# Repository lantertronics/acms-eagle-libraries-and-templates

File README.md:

Here's a set of Eagle files for the benefit of my ECE4450: Analog Circuits for Music Synthesis studnets; hopefully other folks will find them helpful as well.

# Spring 2023: Tangible Waves template

To use acms_project_starter_template, I recommend copying the schematic file and giving it a new filename and deleting the parts you don't need, but *not* copying the board file. Official tangible waves modules use surface mount parts for manufacturability and to keep the size small. Since we're using through-hole parts, we need more space, so I made it three Tangible Waves module units wide (75 millimeters). You can try making this 50 millimeters wide instead if you have a small circuit (change the width to 1.9685 inches and delete the two rightmost mounting holes and then scoot the headers over).

# Spring 2021: Eurorack/MOTM template

To use acms_project_starter_template, I recommend copying the schematic file and giving it a new filename and deleting the parts you don't need, but *not* copying the board file. The board file shows where to put mounting holes (size 0.12587425 = 3.2 mm), but otherwise isn't too useful, since once you start adding your own parts, Eagle will just plunk them down one after another in a straight line going downward. If you place your parts on the schematic first and then tell Eagle to make the PCB, the parts will appear in a nice convenient grid pattern on the side of the PCB.

# Libraries

ota_upgraded.lbr and synthdiy_upgraded.lbr are librraries I found elsewhere that didn't want to open in the newest version of Eagle; apparently the name for layer 88 got scrabled as part of the input process. I just changed the layer name to "weird" to get something that would import without error.

The devices in the aaronXXXX.lbr libraries all have the suffix _AARON; I did that so I can find my custom devices quickly.

The capacitors in the eagle library have a little capacitor symbol on the PCB footprint, and have the cap value outside. I prefer to put the cap value inside the symbol footprint, so I made aaroncap.lbr, which has some capacitor footprints with the cap symbol removed and the value placed inside the capacitor.

aaronlibrary.lbr has an oval PCB pad with a little X for the schematic symbol (IOPAD_AARON), a jack symbol on the schematic for off-board jacks where the PCB has a circular pad for the signal and a square pad for the ground (OFFBOARD2JACKALT_AARON), and symbols for the SSM2210 and SSM2220 matched transistor pairs.

I made aaronpot.lbr to handle some potentiometers where I couldn't find a built-in Eagle symbol that exactly matched it. I can't remember exactly what I made it for.

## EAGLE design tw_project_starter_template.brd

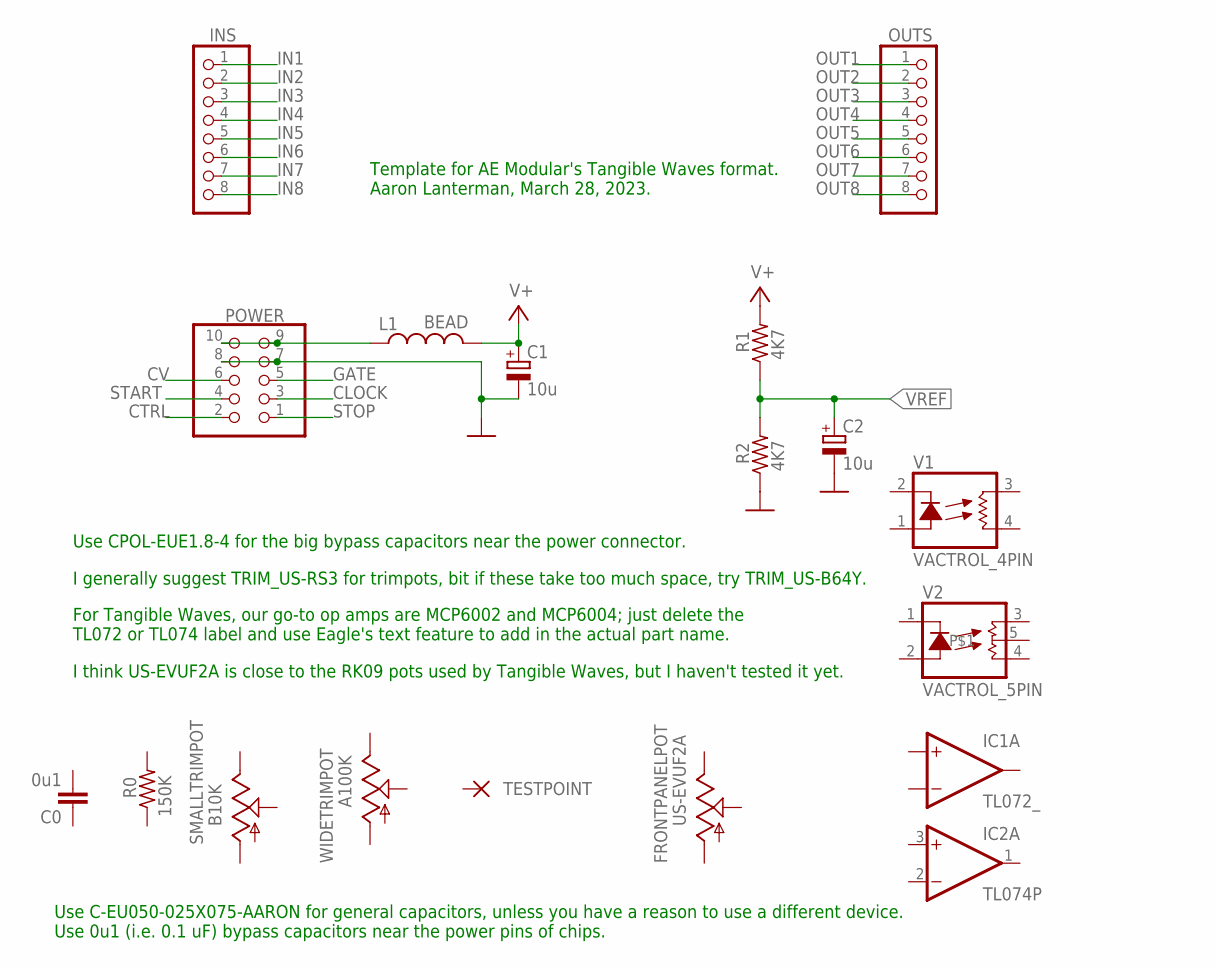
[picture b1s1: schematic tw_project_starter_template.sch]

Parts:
C0: 0u1; C050-025X075-AARON
C1, C2: 10u; E1,8-4
FRONTPANELPOT: US-EVUF2A; EVUF
IC1: TL072_; DIL08
IC2: TL074P; DIL14
INS: PINHD-1X8; 1X08
L1: BEAD; 0207/10
OUTS: PINHD-1X8; 1X08
POWER: PINHD-2X5; 2X05
R0: 150K; 0207/10
R1, R2: 4K7; 0207/10
SMALLTRIMPOT: B10K; B64Y
TESTPOINT: IOPAD_AARON; ELLIPTICALPADSINGLE
V1: VACTROL_4PIN; VACTROL_4PIN_VTL5C
V2: VACTROL_5PIN; VACTROL_5PIN_VTL5C-2
WIDETRIMPOT: A100K; S63P

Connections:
+5V: L1.1, POWER.9, POWER.10
CLOCK: POWER.3
CTRL: POWER.2
CV: POWER.6
GATE: POWER.5
GND: C1.-, C2.-, POWER.7, POWER.8, R2.1
IN1: INS.1
IN2: INS.2
IN3: INS.3
IN4: INS.4
IN5: INS.5
IN6: INS.6
IN7: INS.7
IN8: INS.8
OUT1: OUTS.1
OUT2: OUTS.2
OUT3: OUTS.3
OUT4: OUTS.4
OUT5: OUTS.5
OUT6: OUTS.6
OUT7: OUTS.7
OUT8: OUTS.8
START: POWER.4
STOP: POWER.1
V+: C1.+, IC1.8 (V+), IC2.4 (V+), L1.2, R1.2
V-: IC1.4 (V-), IC2.11 (V-)
VREF: C2.+, R1.1, R2.2

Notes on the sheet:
Template for AE Modular's Tangible Waves format. Aaron Lanterman, March 28, 2023.
Use CPOL-EUE1.8-4 for the big bypass capacitors near the power connector.
Use C-EU050-025X075-AARON for general capacitors, unless you have a reason to use a different device. Use 0u1 (i.e. 0.1 uF) bypass capacitors near the power pins of chips.
I generally suggest TRIM_US-RS3 for trimpots, bit if these take too much space, try TRIM_US-B64Y.
For Tangible Waves, our go-to op amps are MCP6002 and MCP6004; just delete the TL072 or TL074 label and use Eagle's text feature to add in the actual part name.
I think US-EVUF2A is close to the RK09 pots used by Tangible Waves, but I haven't tested it yet.

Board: 2 copper layers, 18 parts (0 on the bottom side), 5 nets, no tracks yet.

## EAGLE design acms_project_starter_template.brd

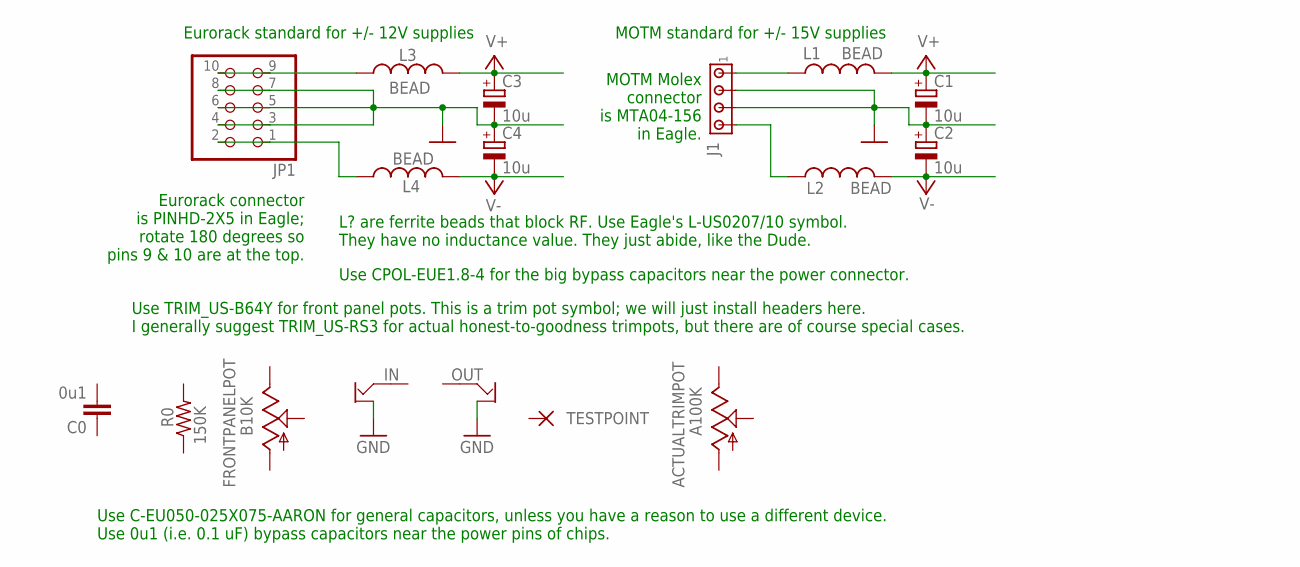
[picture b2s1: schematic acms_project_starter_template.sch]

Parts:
ACTUALTRIMPOT: A100K; RS3
C0: 0u1; C050-025X075-AARON
C1, C2, C3, C4: 10u; E1,8-4
FRONTPANELPOT: B10K; B64Y
IN: OFFBOARD2JACKALT_AARON; OFFBOARD2JACKALT
J1: MTA04-156; 1X4MTA
JP1: PINHD-2X5; 2X05
L1, L2, L3, L4: BEAD; 0207/10
OUT: OFFBOARD2JACKALT_AARON; OFFBOARD2JACKALT
R0: 150K; 0207/10
TESTPOINT: IOPAD_AARON; ELLIPTICALPADSINGLE

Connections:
GND: C1.-, C2.+, C3.-, C4.+, IN.GND, J1.2, J1.3, JP1.3, JP1.4, JP1.5, JP1.6, JP1.7, JP1.8, OUT.GND
unnamed: J1.1, L1.1
unnamed: J1.4, L2.1
unnamed: JP1.9, JP1.10, L3.1
unnamed: JP1.1, JP1.2, L4.1
V+: C1.+, C3.+, L1.2, L3.2
V-: C2.-, C4.-, L2.2, L4.2

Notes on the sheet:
MOTM standard for +/- 15V supplies
L? are ferrite beads that block RF. Use Eagle's L-US0207/10 symbol. They have no inductance value. They just abide, like the Dude.
MOTM Molex connector is MTA04-156 in Eagle.
Eurorack standard for +/- 12V supplies
Eurorack connector is PINHD-2X5 in Eagle; rotate 180 degrees so pins 9 & 10 are at the top.
Use CPOL-EUE1.8-4 for the big bypass capacitors near the power connector.
Use C-EU050-025X075-AARON for general capacitors, unless you have a reason to use a different device. Use 0u1 (i.e. 0.1 uF) bypass capacitors near the power pins of chips.
Use TRIM_US-B64Y for front panel pots. This is a trim pot symbol; we will just install headers here. I generally suggest TRIM_US-RS3 for actual honest-to-goodness trimpots, but there are of course special cases.

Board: 2 copper layers, 17 parts (0 on the bottom side), 7 nets, no tracks yet.
